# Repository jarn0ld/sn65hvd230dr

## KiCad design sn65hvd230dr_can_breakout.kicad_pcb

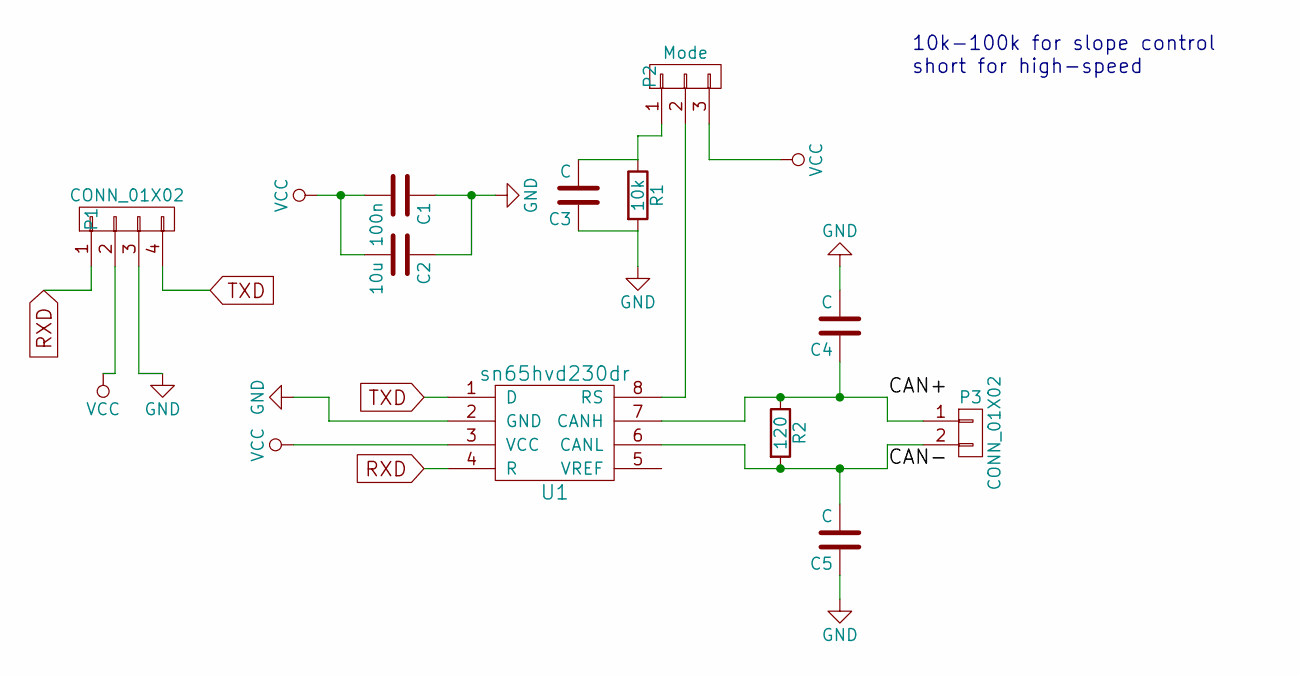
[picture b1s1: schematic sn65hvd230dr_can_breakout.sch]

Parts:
C1: 100n; C_0805_HandSoldering
C2: 10u; C_0805_HandSoldering
C3, C4, C5: C; C_0805_HandSoldering
P1: CONN_01X02; Pin_Header_Angled_1x04
P2: Mode; Pin_Header_Straight_1x03
P3: CONN_01X02; Pin_Header_Angled_1x02
R1: 10k; R_0805_HandSoldering
R2: 120; R_0805_HandSoldering
U1: sn65hvd230dr; SOIC-8-N

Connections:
/CAN+: C4.1, P3.1, R2.1, U1.7 (CANH)
/CAN-: C5.2, P3.2, R2.2, U1.6 (CANL)
GND: C1.1, C2.1, C3.1, C4.2, C5.1, P1.3, R1.2, U1.2 (GND)
unnamed: C3.2, P2.1, R1.1
unnamed: P2.2, U1.8 (RS)
RXD: P1.1, U1.4 (R)
TXD: P1.4, U1.1 (D)
VCC: C1.2, C2.2, P1.2, P2.3, U1.3 (VCC)

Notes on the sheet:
10k-100k for slope control short for high-speed

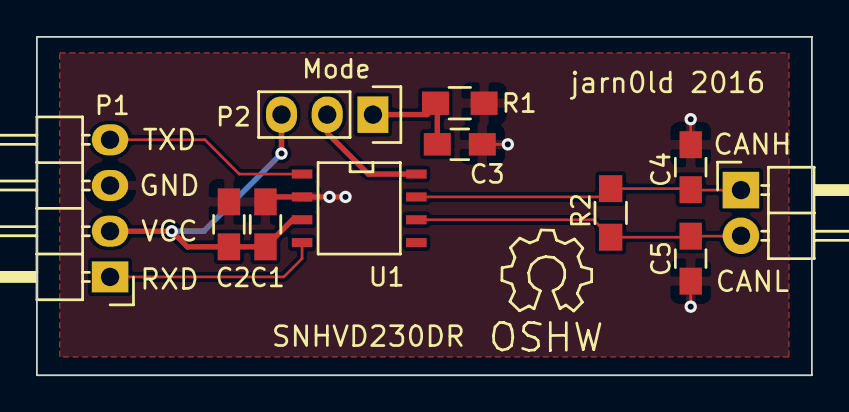
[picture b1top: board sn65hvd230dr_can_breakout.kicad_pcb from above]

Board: 2 copper layers, 43.1 x 18.8 mm, 11 parts (0 on the bottom side), 8 nets.

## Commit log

2016-01-22 fabrication run 1
2016-01-25 set proper oshpark DRs for vias
